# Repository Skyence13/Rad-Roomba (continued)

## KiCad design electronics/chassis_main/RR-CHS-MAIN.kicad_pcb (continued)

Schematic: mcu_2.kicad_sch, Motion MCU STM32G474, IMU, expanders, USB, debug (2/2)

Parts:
C152, C153, C154, C155, C156: 100n; C_0603_1608Metric; MPN CC0603KRX7R9BB104
D38: TPD4E05U06; USON-10_2.5x1.0mm_P0.5mm; MPN TPD4E05U06DQAR
F_AUX: 0.35A; Fuse_1206_3216Metric; MPN 1206L035YR
JP2: SJ open; SolderJumper-2_P1.3mm_Open_RoundedPad1.0x1.5mm; MPN SOLDER-JUMPER
J_AUX: JST GH 3p top; JST_GH_BM03B-GHS-TBT_1x03-1MP_P1.25mm_Vertical; MPN BM03B-GHS-TBT(LF)(SN)
J_NTC: JST GH 4p top; JST_GH_BM04B-GHS-TBT_1x04-1MP_P1.25mm_Vertical; MPN BM04B-GHS-TBT(LF)(SN)
R206, R207, R208, R209: 100k; R_0603_1608Metric; MPN RC0603FR-07100KL
R210: 10k; R_0603_1608Metric; MPN RC0603FR-0710KL
R211, R212, R213, R214: 2.2k; R_0603_1608Metric; MPN RC0603FR-072K2L
R215, R217, R219: 10k; R_0603_1608Metric; MPN RT0603BRD0710KL
R216, R218, R220: 1k; R_0603_1608Metric; MPN RC0603FR-071KL
RT1: 10k NTC; R_0603_1608Metric; MPN NCP18XH103F03RB
U44: TCA9535; TSSOP-24_4.4x7.8mm_P0.65mm; MPN TCA9535PWR
U45, U47: TCA9534; TSSOP-16_4.4x5mm_P0.65mm; MPN TCA9534PWR

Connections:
3V3: C152.1, C153.1, R210.1, R211.1, R212.1, R213.1, R214.1, U44.24 (VCC), U45.1 (A0), U45.16 (VDD), U47.2 (A1), U47.16 (VDD); also elsewhere on the board
BUS_CLAMP_ACTIVE: U47.7 (P3); also elsewhere on the board
CHAIN_END_RB: U44.20 (P17); also elsewhere on the board
CHG_NSMBALERT: U45.10 (P5); also elsewhere on the board
CHN6A_RB: U47.11 (P6); also elsewhere on the board
CHS_HTR_NFLT: U45.6 (P2); also elsewhere on the board
DBG_RX_C: D38.5 (D2-); also elsewhere on the board
DBG_TX_C: D38.4 (D2+); also elsewhere on the board
GND: C152.2, C153.2, C154.2, C155.2, C156.2, D38.3 (GND), D38.8 (GND), J_AUX.2, J_AUX.MP (MountPin), J_NTC.2, J_NTC.4, J_NTC.MP (MountPin), R206.2, R207.2, R208.2, R209.2, RT1.2, U44.2 (A1), U44.3 (A2), U44.12 (GND), U44.21 (A0), U45.2 (A1), U45.3 (A2), U45.8 (GND), U47.1 (A0), U47.3 (A2), U47.8 (GND); also elsewhere on the board
HEAD_HTR_NFLT: U45.5 (P1); also elsewhere on the board
HEAD_LOOP2_OK_RB: U47.6 (P2); also elsewhere on the board
HEAD_PWR_EN: U44.13 (P10); also elsewhere on the board
HEAD_PWR_NFLT: U45.4 (P0); also elsewhere on the board
I2C_SYS_SCL: R212.2, U44.22 (SCL), U45.14 (SCL), U47.14 (SCL); also elsewhere on the board
I2C_SYS_SDA: R211.2, U44.23 (SDA), U45.15 (SDA), U47.15 (SDA); also elsewhere on the board
I2C_TOF_SCL: R214.2; also elsewhere on the board
I2C_TOF_SDA: R213.2; also elsewhere on the board
LAMP_PAUSE: U44.10 (P06); also elsewhere on the board
LAMP_REARM: U44.9 (P05); also elsewhere on the board
LATCH_NC_RB: U47.4 (P0); also elsewhere on the board
LATCH_RUN_RB: U47.5 (P1); also elsewhere on the board
LED_CHARGE: U44.8 (P04); also elsewhere on the board
LED_FAULT: U44.7 (P03); also elsewhere on the board
LED_HOLD: U44.6 (P02); also elsewhere on the board
LED_MOVING: U44.5 (P01); also elsewhere on the board
LED_READY: U44.4 (P00); also elsewhere on the board
LED_STAT2: U44.11 (P07); also elsewhere on the board
LOOP_TEST_A: U47.9 (P4); also elsewhere on the board
LOOP_TEST_B: U47.12 (P7); also elsewhere on the board
NTC_BAY: D38.1 (D1+), J_NTC.1, R215.2, R216.1
NTC_BAY_ADC: C154.1, R216.2; also elsewhere on the board
NTC_BOARD_ADC: C156.1, R219.2, RT1.1; also elsewhere on the board
NTC_PACK: D38.2 (D1-), J_NTC.3, R217.2, R218.1
NTC_PACK_ADC: C155.1, R218.2; also elsewhere on the board
PMON_NALERT: R210.2, U45.11 (P6); also elsewhere on the board
SET_READY_RB: U47.10 (P5); also elsewhere on the board
SPARE_IO: J_AUX.3, R220.2
SPARE_IO_R: JP2.2 (B), R220.1
SWO_SPARE: JP2.1 (A); also elsewhere on the board
TOF_MUX_NRST: R209.1, U44.19 (P16); also elsewhere on the board
TOF_XSHUT_CLIFF: R206.1, U44.16 (P13); also elsewhere on the board
TOF_XSHUT_LOOK: R207.1, U44.17 (P14); also elsewhere on the board
TOF_XSHUT_REAR: R208.1, U44.18 (P15); also elsewhere on the board
V5_CM5_NFLT: U45.9 (P4); also elsewhere on the board
V5_CM5_OFF_REQ: U44.15 (P12); also elsewhere on the board
V5_PGOOD: U45.12 (P7); also elsewhere on the board
V12_AUX: F_AUX.2, J_AUX.1; also elsewhere on the board
V12_LIDAR_EN: U44.14 (P11); also elsewhere on the board
V12_LIDAR_NFLT: U45.7 (P3); also elsewhere on the board
VBAT_SW: F_AUX.1; also elsewhere on the board
VREF_3V0: R215.1, R217.1, R219.1; also elsewhere on the board

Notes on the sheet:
Motion MCU STM32G474, IMU, expanders, USB, debug (2/2)

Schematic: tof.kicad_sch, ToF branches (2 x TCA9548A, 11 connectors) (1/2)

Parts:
C157, C158, C159, C160, C161, C162, C163, C164: 100n; C_0603_1608Metric; MPN CC0603KRX7R9BB104
D39, D40, D41, D42, D43: TPD4E05U06; USON-10_2.5x1.0mm_P0.5mm; MPN TPD4E05U06DQAR
FB5, FB6, FB7, FB8, FB9, FB10: 600R; L_0603_1608Metric; MPN BLM18KG601SN1D
J_TOF0, J_TOF1, J_TOF2, J_TOF3, J_TOF4, J_TOF5: JST GH 6p top; JST_GH_BM06B-GHS-TBT_1x06-1MP_P1.25mm_Vertical; MPN BM06B-GHS-TBT(LF)(SN)
R221, R222, R226, R227, R231, R232, R236, R237, R241, R242, R246: 100; R_0603_1608Metric; MPN RC0603FR-07100RL
R223, R224, R228, R229, R233, R234, R238, R239, R243, R244: 2.2k; R_0603_1608Metric; MPN RC0603FR-072K2L
R225, R230, R235, R240, R245: 1k; R_0603_1608Metric; MPN RC0603FR-071KL
TP12: TOF0_GPIO1; TestPoint_Keystone_5019_Miniature; MPN 5019
TP13: TOF1_GPIO1; TestPoint_Keystone_5019_Miniature; MPN 5019
TP14: TOF2_GPIO1; TestPoint_Keystone_5019_Miniature; MPN 5019
TP15: TOF3_GPIO1; TestPoint_Keystone_5019_Miniature; MPN 5019
TP16: TOF4_GPIO1; TestPoint_Keystone_5019_Miniature; MPN 5019
U50, U51: TCA9548A; TSSOP-24_4.4x7.8mm_P0.65mm; MPN TCA9548APWR

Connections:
3V3: C157.1, C158.1, FB5.1, FB6.1, FB7.1, FB8.1, FB9.1, FB10.1, R223.1, R224.1, R228.1, R229.1, R233.1, R234.1, R238.1, R239.1, R243.1, R244.1, U50.24 (VCC), U51.1 (A0), U51.24 (VCC); also elsewhere on the board
GND: C157.2, C158.2, C159.2, C160.2, C161.2, C162.2, C163.2, C164.2, D39.3 (GND), D39.8 (GND), D40.3 (GND), D40.8 (GND), D41.3 (GND), D41.8 (GND), D42.3 (GND), D42.8 (GND), D43.3 (GND), D43.8 (GND), J_TOF0.2, J_TOF0.MP (MountPin), J_TOF1.2, J_TOF1.MP (MountPin), J_TOF2.2, J_TOF2.MP (MountPin), J_TOF3.2, J_TOF3.MP (MountPin), J_TOF4.2, J_TOF4.MP (MountPin), J_TOF5.2, J_TOF5.MP (MountPin), U50.1 (A0), U50.2 (A1), U50.12 (GND), U50.21 (A2), U51.2 (A1), U51.12 (GND), U51.21 (A2); also elsewhere on the board
I2C_TOF_SCL: U50.22 (SCL), U51.22 (SCL); also elsewhere on the board
I2C_TOF_SDA: U50.23 (SDA), U51.23 (SDA); also elsewhere on the board
TOF0_3V3: C159.1, FB5.2, J_TOF0.1
TOF0_GPIO1: D39.5 (D2-), J_TOF0.6, TP12.1
TOF00_SCL: R222.1, R224.2, U50.5 (SC0)
TOF0_SCL_C: D39.2 (D1-), J_TOF0.4, R222.2
TOF00_SDA: R221.1, R223.2, U50.4 (SD0)
TOF0_SDA_C: D39.1 (D1+), J_TOF0.3, R221.2
TOF0_XSHUT_C: D39.4 (D2+), J_TOF0.5, R225.2
TOF1_3V3: C160.1, FB6.2, J_TOF1.1
TOF1_GPIO1: D40.5 (D2-), J_TOF1.6, TP13.1
TOF01_SCL: R232.1, R234.2, U50.7 (SC1)
TOF1_SCL_C: D40.2 (D1-), J_TOF1.4, R227.2
TOF01_SDA: R231.1, R233.2, U50.6 (SD1)
TOF1_SDA_C: D40.1 (D1+), J_TOF1.3, R226.2
TOF1_XSHUT_C: D40.4 (D2+), J_TOF1.5, R230.2
TOF2_3V3: C161.1, FB7.2, J_TOF2.1
TOF2_GPIO1: D41.5 (D2-), J_TOF2.6, TP14.1
TOF02_SCL: R242.1, R244.2, U50.9 (SC2)
TOF2_SCL_C: D41.2 (D1-), J_TOF2.4, R232.2
TOF02_SDA: R241.1, R243.2, U50.8 (SD2)
TOF2_SDA_C: D41.1 (D1+), J_TOF2.3, R231.2
TOF2_XSHUT_C: D41.4 (D2+), J_TOF2.5, R235.2
TOF3_3V3: C162.1, FB8.2, J_TOF3.1
TOF3_GPIO1: D42.5 (D2-), J_TOF3.6, TP15.1
TOF03_SCL: U50.11 (SC3); also elsewhere on the board
TOF3_SCL_C: D42.2 (D1-), J_TOF3.4, R237.2
TOF03_SDA: U50.10 (SD3); also elsewhere on the board
TOF3_SDA_C: D42.1 (D1+), J_TOF3.3, R236.2
TOF3_XSHUT_C: D42.4 (D2+), J_TOF3.5, R240.2
TOF4_3V3: C163.1, FB9.2, J_TOF4.1
TOF4_GPIO1: D43.5 (D2-), J_TOF4.6, TP16.1
TOF04_SCL: U50.14 (SC4); also elsewhere on the board
TOF4_SCL_C: D43.2 (D1-), J_TOF4.4, R242.2
TOF04_SDA: U50.13 (SD4); also elsewhere on the board
TOF4_SDA_C: D43.1 (D1+), J_TOF4.3, R241.2
TOF4_XSHUT_C: D43.4 (D2+), J_TOF4.5, R245.2
TOF5_3V3: C164.1, FB10.2, J_TOF5.1
TOF5_GPIO1: J_TOF5.6; also elsewhere on the board
TOF05_SCL: U50.16 (SC5); also elsewhere on the board
TOF5_SCL_C: J_TOF5.4; also elsewhere on the board
TOF05_SDA: U50.15 (SD5); also elsewhere on the board
TOF5_SDA_C: J_TOF5.3, R246.2; also elsewhere on the board
TOF5_XSHUT_C: J_TOF5.5; also elsewhere on the board
TOF10_SCL: R227.1, R229.2, U51.5 (SC0)
TOF10_SDA: R226.1, R228.2, U51.4 (SD0)
TOF11_SCL: R237.1, R239.2, U51.7 (SC1)
TOF11_SDA: R236.1, R238.2, U51.6 (SD1)
TOF12_SCL: U51.9 (SC2); also elsewhere on the board
TOF12_SDA: R246.1, U51.8 (SD2); also elsewhere on the board
TOF13_SCL: U51.11 (SC3); also elsewhere on the board
TOF13_SDA: U51.10 (SD3); also elsewhere on the board
TOF14_SCL: U51.14 (SC4); also elsewhere on the board
TOF14_SDA: U51.13 (SD4); also elsewhere on the board
TOF_MUX_NRST: U50.3 (~RESET), U51.3 (~RESET); also elsewhere on the board
TOF_XSHUT_CLIFF: R225.1, R230.1, R235.1, R240.1; also elsewhere on the board
TOF_XSHUT_LOOK: R245.1; also elsewhere on the board

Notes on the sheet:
ToF branches (2 x TCA9548A, 11 connectors) (1/2)

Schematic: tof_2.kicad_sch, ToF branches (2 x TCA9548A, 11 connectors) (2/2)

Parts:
C165, C166, C167, C168, C169: 100n; C_0603_1608Metric; MPN CC0603KRX7R9BB104
D44, D45, D46, D47, D48, D49: TPD4E05U06; USON-10_2.5x1.0mm_P0.5mm; MPN TPD4E05U06DQAR
FB11, FB12, FB13, FB14, FB15: 600R; L_0603_1608Metric; MPN BLM18KG601SN1D
J_TOF6, J_TOF7, J_TOF8, J_TOF9, J_TOF10: JST GH 6p top; JST_GH_BM06B-GHS-TBT_1x06-1MP_P1.25mm_Vertical; MPN BM06B-GHS-TBT(LF)(SN)
R247, R251, R252, R256, R257, R261, R262, R266, R267, R271, R272: 100; R_0603_1608Metric; MPN RC0603FR-07100RL
R248, R249, R253, R254, R258, R259, R263, R264, R268, R269, R273, R274: 2.2k; R_0603_1608Metric; MPN RC0603FR-072K2L
R250, R255, R260, R265, R270, R275: 1k; R_0603_1608Metric; MPN RC0603FR-071KL
TP17: TOF5_GPIO1; TestPoint_Keystone_5019_Miniature; MPN 5019
TP18: TOF6_GPIO1; TestPoint_Keystone_5019_Miniature; MPN 5019
TP19: TOF7_GPIO1; TestPoint_Keystone_5019_Miniature; MPN 5019
TP20: TOF8_GPIO1; TestPoint_Keystone_5019_Miniature; MPN 5019
TP21: TOF9_GPIO1; TestPoint_Keystone_5019_Miniature; MPN 5019
TP22: TOF10_GPIO1; TestPoint_Keystone_5019_Miniature; MPN 5019

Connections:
3V3: FB11.1, FB12.1, FB13.1, FB14.1, FB15.1, R248.1, R249.1, R253.1, R254.1, R258.1, R259.1, R263.1, R264.1, R268.1, R269.1, R273.1, R274.1; also elsewhere on the board
GND: C165.2, C166.2, C167.2, C168.2, C169.2, D44.3 (GND), D44.8 (GND), D45.3 (GND), D45.8 (GND), D46.3 (GND), D46.8 (GND), D47.3 (GND), D47.8 (GND), D48.3 (GND), D48.8 (GND), D49.3 (GND), D49.8 (GND), J_TOF6.2, J_TOF6.MP (MountPin), J_TOF7.2, J_TOF7.MP (MountPin), J_TOF8.2, J_TOF8.MP (MountPin), J_TOF9.2, J_TOF9.MP (MountPin), J_TOF10.2, J_TOF10.MP (MountPin); also elsewhere on the board
TOF03_SCL: R252.1, R254.2; also elsewhere on the board
TOF03_SDA: R251.1, R253.2; also elsewhere on the board
TOF04_SCL: R262.1, R264.2; also elsewhere on the board
TOF04_SDA: R261.1, R263.2; also elsewhere on the board
TOF5_GPIO1: D44.5 (D2-), TP17.1; also elsewhere on the board
TOF05_SCL: R272.1, R274.2; also elsewhere on the board
TOF5_SCL_C: D44.2 (D1-), R247.2; also elsewhere on the board
TOF05_SDA: R271.1, R273.2; also elsewhere on the board
TOF5_SDA_C: D44.1 (D1+); also elsewhere on the board
TOF5_XSHUT_C: D44.4 (D2+), R250.2; also elsewhere on the board
TOF6_3V3: C165.1, FB11.2, J_TOF6.1
TOF6_GPIO1: D45.5 (D2-), J_TOF6.6, TP18.1
TOF6_SCL_C: D45.2 (D1-), J_TOF6.4, R252.2
TOF6_SDA_C: D45.1 (D1+), J_TOF6.3, R251.2
TOF6_XSHUT_C: D45.4 (D2+), J_TOF6.5, R255.2
TOF7_3V3: C166.1, FB12.2, J_TOF7.1
TOF7_GPIO1: D46.5 (D2-), J_TOF7.6, TP19.1
TOF7_SCL_C: D46.2 (D1-), J_TOF7.4, R257.2
TOF7_SDA_C: D46.1 (D1+), J_TOF7.3, R256.2
TOF7_XSHUT_C: D46.4 (D2+), J_TOF7.5, R260.2
TOF8_3V3: C167.1, FB13.2, J_TOF8.1
TOF8_GPIO1: D47.5 (D2-), J_TOF8.6, TP20.1
TOF8_SCL_C: D47.2 (D1-), J_TOF8.4, R262.2
TOF8_SDA_C: D47.1 (D1+), J_TOF8.3, R261.2
TOF8_XSHUT_C: D47.4 (D2+), J_TOF8.5, R265.2
TOF9_3V3: C168.1, FB14.2, J_TOF9.1
TOF9_GPIO1: D48.5 (D2-), J_TOF9.6, TP21.1
TOF9_SCL_C: D48.2 (D1-), J_TOF9.4, R267.2
TOF9_SDA_C: D48.1 (D1+), J_TOF9.3, R266.2
TOF9_XSHUT_C: D48.4 (D2+), J_TOF9.5, R270.2
TOF10_3V3: C169.1, FB15.2, J_TOF10.1
TOF10_GPIO1: D49.5 (D2-), J_TOF10.6, TP22.1
TOF10_SCL_C: D49.2 (D1-), J_TOF10.4, R272.2
TOF10_SDA_C: D49.1 (D1+), J_TOF10.3, R271.2
TOF10_XSHUT_C: D49.4 (D2+), J_TOF10.5, R275.2
TOF12_SCL: R247.1, R249.2; also elsewhere on the board
TOF12_SDA: R248.2; also elsewhere on the board
TOF13_SCL: R257.1, R259.2; also elsewhere on the board
TOF13_SDA: R256.1, R258.2; also elsewhere on the board
TOF14_SCL: R267.1, R269.2; also elsewhere on the board
TOF14_SDA: R266.1, R268.2; also elsewhere on the board
TOF_XSHUT_LOOK: R250.1, R255.1, R260.1; also elsewhere on the board
TOF_XSHUT_REAR: R265.1, R270.1, R275.1; also elsewhere on the board

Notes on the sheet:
ToF branches (2 x TCA9548A, 11 connectors) (2/2)

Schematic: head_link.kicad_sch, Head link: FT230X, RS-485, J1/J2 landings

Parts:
C170, C171: 47p; C_0603_1608Metric; MPN CC0603JRNPO9BN470
C172: 4.7u; C_0805_2012Metric; MPN GRM21BR71C475KA73L
C173, C174, C175: 100n; C_0603_1608Metric; MPN CC0603KRX7R9BB104
D50: BAT54; D_SOD-123; MPN BAT54W-7-F
D60: SM712; SOT-23; MPN SM712.TCT
FB_U: 600R; L_0603_1608Metric; MPN BLM18KG601SN1D
J_HEAD1: Mini-Fit Jr 2x5 RA; Molex_Mini-Fit_Jr_5569-10A2_2x05_P4.20mm_Horizontal; MPN 39-30-1100
J_HEAD2: JST GH 8p side; JST_GH_SM08B-GHS-TB_1x08-1MP_P1.25mm_Horizontal; MPN SM08B-GHS-TB(LF)(SN)
J_USB_HEAD: JST GH 5p top; JST_GH_BM05B-GHS-TBT_1x05-1MP_P1.25mm_Vertical; MPN BM05B-GHS-TBT(LF)(SN)
L60: CMC 90R; L_CommonModeChoke_Coilank_ACM2012; MPN ACM2012-900-2P-T002
LED2: green; LED_0603_1608Metric; MPN 150060GS75000
NT1: net tie; NetTie-2_SMD_Pad2.0mm; MPN NET-TIE
R276, R277: 27; R_0603_1608Metric; MPN RC0603FR-0727RL
R278, R279, R280: 1k; R_0603_1608Metric; MPN RC0603FR-071KL
R281, R282: 10k; R_0603_1608Metric; MPN RC0603FR-0710KL
R283: 4.7k; R_0603_1608Metric; MPN RC0603FR-074K7L
R284: 120; R_0805_2012Metric; MPN RC0805FR-07120RL
R285, R286: 560; R_0805_2012Metric; MPN RC0805FR-07560RL
R287, R288: 10; R_0805_2012Metric; MPN RC0805FR-0710RL
R289: 120; R_0805_2012Metric; MPN RC0805FR-07120RL; not fitted
R290: 10k; R_0603_1608Metric; MPN RC0603FR-0710KL; not fitted
TP23: SYNC_TTL; TestPoint_Keystone_5019_Miniature; MPN 5019
U60: USBLC6-2SC6; SOT-23-6; MPN USBLC6-2SC6
U61: FT230XS; SSOP-16_3.9x4.9mm_P0.635mm; MPN FT230XS-R
U62: THVD1450; SOIC-8_3.9x4.9mm_P1.27mm; MPN THVD1450DR
U63: THVD1450; SOIC-8_3.9x4.9mm_P1.27mm; MPN THVD1450DR; not fitted

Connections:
BUS_5V: J_HEAD2.3; also elsewhere on the board
FT_3V3: C174.1, R278.1, R283.1, U61.3 (VCCIO), U61.10 (3V3OUT)
FT_DM: C171.1, R277.2, U61.9 (USBDM)
FT_DP: C170.1, R276.2, U61.8 (USBDP)
FT_LED_A: LED2.2 (A), R278.2
FT_LED_N: LED2.1 (K), U61.7 (CBUS2)
FT_RXD: D50.2 (A), R283.2, U61.4 (RXD)
FT_TXD: R279.1, U61.1 (TXD)
FT_TXDEN: R280.1, U61.15 (CBUS0); also elsewhere on the board
FT_TXDEN_R: R280.2, R281.1, U62.2 (~RE), U62.3 (DE)
FT_TXD_R: R279.2, R282.2, U62.4 (DI)
FT_VCC: C172.1, C173.1, FB_U.2, U61.11 (~RESET), U61.12 (VCC)
GND: C170.2, C171.2, C172.2, C173.2, C174.2, C175.2, D60.3 (GND), J_HEAD1.2, J_HEAD2.4, J_HEAD2.MP (MountPin), J_USB_HEAD.4, J_USB_HEAD.MP (MountPin), NT1.2, R281.2, R286.2, R290.2, U60.2 (GND), U61.5 (GND), U61.6 (~CTS), U61.13 (GND), U62.5 (GND), U63.5 (GND); also elsewhere on the board
HEAD_HTR_N: J_HEAD1.4, NT1.1
HEAD_HTR_P: J_HEAD1.3; also elsewhere on the board
HEAD_LOOP_OUT: J_HEAD1.5; also elsewhere on the board
HEAD_LOOP_RET: J_HEAD1.6; also elsewhere on the board
HEAD_PRES_ID: J_HEAD1.7; also elsewhere on the board
HEAD_PWR_P: J_HEAD1.1; also elsewhere on the board
HUSBC_DM: J_USB_HEAD.2, U60.1 (I/O1)
HUSBC_DP: J_USB_HEAD.3, U60.3 (I/O2)
HUSB_DM_R: R277.1, U60.6 (I/O1)
HUSB_DP_R: R276.1, U60.4 (I/O2)
HUSB_VBUS: FB_U.1, J_USB_HEAD.1, U60.5 (VBUS)
J2_PRES: J_HEAD2.7; also elsewhere on the board
RS485_DN: D60.2 (IO2), J_HEAD2.2, L60.3
RS485_DP: D60.1 (IO1), J_HEAD2.1, L60.2
RS_A: R284.1, R285.2, R287.1, U62.6 (A)
RS_A_L: L60.1, R287.2
RS_B: R284.2, R286.1, R288.1, U62.7 (B)
RS_B_L: L60.4, R288.2
RS_RO: D50.1 (K), U62.1 (RO); also elsewhere on the board
SYNC_N: J_HEAD2.6, R289.2, U63.7 (B)
SYNC_P: J_HEAD2.5, R289.1, U63.6 (A)
SYNC_TTL: R290.1, TP23.1, U63.4 (DI)
USB_SHLD: J_USB_HEAD.5; also elsewhere on the board
V5_AUX: C175.1, R282.1, R285.1, U62.8 (VCC), U63.2 (~RE), U63.3 (DE), U63.8 (VCC); also elsewhere on the board

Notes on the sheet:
Head link: FT230X, RS-485, J1/J2 landings
S2-02: J_HEAD1 is a Mini-Fit Jr 2x5 (AWG 18 contacts for the heater pair); pins 1-8 = J1 pins 1-8, pins 9/10 NC.

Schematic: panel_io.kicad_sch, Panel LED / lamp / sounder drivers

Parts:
J_PANEL: JST GH 10p top; JST_GH_BM10B-GHS-TBT_1x10-1MP_P1.25mm_Vertical; MPN BM10B-GHS-TBT(LF)(SN)
LED3: red; LED_0603_1608Metric; MPN 150060RS75000
Q50, Q51, Q52, Q53, Q54, Q55, Q56, Q57, Q58: BSS138; SOT-23; MPN BSS138
R291, R292, R293, R294, R295, R296, R297: 100k; R_0603_1608Metric; MPN RC0603FR-07100KL
R298: 10k; R_0603_1608Metric; MPN RC0603FR-0710KL
R299: 1k; R_0603_1608Metric; MPN RC0603FR-071KL

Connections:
3V3: R299.1; also elsewhere on the board
BUZZER: Q58.1 (G), R298.1; also elsewhere on the board
BUZ_N: J_PANEL.9, Q58.3 (D)
GND: J_PANEL.3, J_PANEL.10, J_PANEL.MP (MountPin), Q50.2 (S), Q51.2 (S), Q52.2 (S), Q53.2 (S), Q54.2 (S), Q55.2 (S), Q56.2 (S), Q57.2 (S), Q58.2 (S), R291.2, R292.2, R293.2, R294.2, R295.2, R296.2, R297.2, R298.2; also elsewhere on the board
LAMP_PAUSE: Q56.1 (G), R297.1; also elsewhere on the board
LAMP_PAUSE_K: Q56.3 (D); also elsewhere on the board
LAMP_REARM: Q55.1 (G), R296.1; also elsewhere on the board
LAMP_REARM_K: Q55.3 (D); also elsewhere on the board
LED_CHARGE: Q54.1 (G), R295.1; also elsewhere on the board
LED_CHARGE_K: J_PANEL.8, Q54.3 (D)
LED_FAULT: Q53.1 (G), R294.1; also elsewhere on the board
LED_FAULT_K: J_PANEL.7, Q53.3 (D), Q57.3 (D)
LED_HOLD: Q52.1 (G), R293.1; also elsewhere on the board
LED_HOLD_K: J_PANEL.6, Q52.3 (D)
LED_MOVING: Q51.1 (G), R292.1; also elsewhere on the board
LED_MOVING_K: J_PANEL.5, Q51.3 (D)
LED_READY: Q50.1 (G), R291.1; also elsewhere on the board
LED_READY_K: J_PANEL.4, Q50.3 (D)
LED_STAT2: LED3.1 (K); also elsewhere on the board
LED_STAT2_A: LED3.2 (A), R299.2
V5_AUX: J_PANEL.1; also elsewhere on the board
V12_AUX: J_PANEL.2; also elsewhere on the board
WDG_FAULT: Q57.1 (G); also elsewhere on the board

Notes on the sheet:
Panel LED / lamp / sounder drivers

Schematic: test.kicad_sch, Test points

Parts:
TP24: WDG_STROBE; TestPoint_Keystone_5019_Miniature; MPN 5019
TP25: WDG_OK; TestPoint_Keystone_5019_Miniature; MPN 5019
TP26: ARM_PERMIT; TestPoint_Keystone_5019_Miniature; MPN 5019
TP27: HW_LATCH_RB; TestPoint_Keystone_5019_Miniature; MPN 5019
TP28: VMOT_SENSE; TestPoint_Keystone_5019_Miniature; MPN 5019
TP29: IPROPI_L; TestPoint_Keystone_5019_Miniature; MPN 5019
TP30: IPROPI_R; TestPoint_Keystone_5019_Miniature; MPN 5019
TP31: SPI1_SCK; TestPoint_Keystone_5019_Miniature; MPN 5019
TP32: SPI1_MISO; TestPoint_Keystone_5019_Miniature; MPN 5019
TP33: SPI1_MOSI; TestPoint_Keystone_5019_Miniature; MPN 5019
TP34: I2C_SYS_SDA; TestPoint_Keystone_5019_Miniature; MPN 5019
TP35: I2C_SYS_SCL; TestPoint_Keystone_5019_Miniature; MPN 5019
TP36: I2C_TOF_SDA; TestPoint_Keystone_5019_Miniature; MPN 5019
TP37: I2C_TOF_SCL; TestPoint_Keystone_5019_Miniature; MPN 5019
TP38: CHAIN_END; TestPoint_Keystone_5019_Miniature; MPN 5019
TP39: RUN_12V; TestPoint_Keystone_5019_Miniature; MPN 5019
TP40: COIL_RTN; TestPoint_Keystone_5019_Miniature; MPN 5019
TP41: VBAT_SW; TestPoint_Keystone_5019_Miniature; MPN 5019
TP42: VSYS; TestPoint_Keystone_5019_Miniature; MPN 5019
TP43: V5_CM5; TestPoint_Keystone_5019_Miniature; MPN 5019
TP44: 3V3; TestPoint_Keystone_5019_Miniature; MPN 5019
TP45: V5_AUX; TestPoint_Keystone_5019_Miniature; MPN 5019
TP46: VREF_3V0; TestPoint_Keystone_5019_Miniature; MPN 5019
TP47: VMOT; TestPoint_Keystone_5019_Miniature; MPN 5019
TP48, TP49: GND; TestPoint_Keystone_5019_Miniature; MPN 5019
TP50: CH_N0; TestPoint_Keystone_5019_Miniature; MPN 5019
TP51: EN_SYS; TestPoint_Keystone_5019_Miniature; MPN 5019
TP52: LOOP_F; TestPoint_Keystone_5019_Miniature; MPN 5019
TP53: PRES_F; TestPoint_Keystone_5019_Miniature; MPN 5019
TP54: CHG_TEMP_OK; TestPoint_Keystone_5019_Miniature; MPN 5019
TP55: CLAMP_G; TestPoint_Keystone_5019_Miniature; MPN 5019
TP56: FT_TXDEN; TestPoint_Keystone_5019_Miniature; MPN 5019
TP57: RS_RO; TestPoint_Keystone_5019_Miniature; MPN 5019
TP58: U3_NTC; TestPoint_Keystone_5019_Miniature; MPN 5019
TP59: V12_AUX; TestPoint_Keystone_5019_Miniature; MPN 5019
TP60: CH_N6A; TestPoint_Keystone_5019_Miniature; MPN 5019
TP61: K1_RUN; TestPoint_Keystone_5019_Miniature; MPN 5019
TP62: RELAY_RTN; TestPoint_Keystone_5019_Miniature; MPN 5019
TP63: SVC1 GND; TestPoint_Pad_D1.5mm; MPN TEST-PAD
TP64: SVC2 SVC_CHAIN_END; TestPoint_Pad_D1.5mm; MPN TEST-PAD
TP65: SVC3 SVC_K1_RUN; TestPoint_Pad_D1.5mm; MPN TEST-PAD
TP66: SVC4 SVC_RUN_HD; TestPoint_Pad_D1.5mm; MPN TEST-PAD
TP67: SVC5 SVC_RUN_12V; TestPoint_Pad_D1.5mm; MPN TEST-PAD
TP68: SVC6 SVC_RELAY_RTN; TestPoint_Pad_D1.5mm; MPN TEST-PAD
TP69: SVC7 SVC_HOLD_A; TestPoint_Pad_D1.5mm; MPN TEST-PAD
TP70: SVC8 SVC_LS_A; TestPoint_Pad_D1.5mm; MPN TEST-PAD
TP71: SVC9 SVC_CH_N6A; TestPoint_Pad_D1.5mm; MPN TEST-PAD
TP72: SVC10 SVC_SET_CAP; TestPoint_Pad_D1.5mm; MPN TEST-PAD

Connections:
3V3: TP44.1; also elsewhere on the board
ARM_PERMIT: TP26.1; also elsewhere on the board
CHAIN_END: TP38.1; also elsewhere on the board
CHG_TEMP_OK: TP54.1; also elsewhere on the board
CH_N0: TP50.1; also elsewhere on the board
CH_N6A: TP60.1; also elsewhere on the board
CLAMP_G: TP55.1; also elsewhere on the board
COIL_RTN: TP40.1; also elsewhere on the board
EN_SYS: TP51.1; also elsewhere on the board
FT_TXDEN: TP56.1; also elsewhere on the board
GND: TP48.1, TP49.1, TP63.1; also elsewhere on the board
HW_LATCH_RB: TP27.1; also elsewhere on the board
I2C_SYS_SCL: TP35.1; also elsewhere on the board
I2C_SYS_SDA: TP34.1; also elsewhere on the board
I2C_TOF_SCL: TP37.1; also elsewhere on the board
I2C_TOF_SDA: TP36.1; also elsewhere on the board
IPROPI_L: TP29.1; also elsewhere on the board
IPROPI_R: TP30.1; also elsewhere on the board
K1_RUN: TP61.1; also elsewhere on the board
LOOP_F: TP52.1; also elsewhere on the board
PRES_F: TP53.1; also elsewhere on the board
RELAY_RTN: TP62.1; also elsewhere on the board
RS_RO: TP57.1; also elsewhere on the board
RUN_12V: TP39.1; also elsewhere on the board
SPI1_MISO: TP32.1; also elsewhere on the board
SPI1_MOSI: TP33.1; also elsewhere on the board
SPI1_SCK: TP31.1; also elsewhere on the board
SVC_CHAIN_END: TP64.1; also elsewhere on the board
SVC_CH_N6A: TP71.1; also elsewhere on the board
SVC_HOLD_A: TP69.1; also elsewhere on the board
SVC_K1_RUN: TP65.1; also elsewhere on the board
SVC_LS_A: TP70.1; also elsewhere on the board
SVC_RELAY_RTN: TP68.1; also elsewhere on the board
SVC_RUN_12V: TP67.1; also elsewhere on the board
SVC_RUN_HD: TP66.1; also elsewhere on the board
SVC_SET_CAP: TP72.1; also elsewhere on the board
U3_NTC: TP58.1; also elsewhere on the board
V5_AUX: TP45.1; also elsewhere on the board
V5_CM5: TP43.1; also elsewhere on the board
V12_AUX: TP59.1; also elsewhere on the board
VBAT_SW: TP41.1; also elsewhere on the board
VMOT: TP47.1; also elsewhere on the board
VMOT_SENSE: TP28.1; also elsewhere on the board
VREF_3V0: TP46.1; also elsewhere on the board
VSYS: TP42.1; also elsewhere on the board
WDG_OK: TP25.1; also elsewhere on the board
WDG_STROBE: TP24.1; also elsewhere on the board

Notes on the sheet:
Test points

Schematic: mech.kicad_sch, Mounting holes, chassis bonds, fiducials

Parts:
C176, C177, C178, C179: 10n; C_0603_1608Metric; MPN CC0603KRX7R9BB103
FID1, FID2, FID3: fiducial; Fiducial_1mm_Mask2mm; MPN FIDUCIAL
H1, H2, H3, H4, H5, H6: M3; MountingHole_3.2mm_M3_Pad_Via; MPN MOUNTING-HOLE-M3
R300, R301, R302, R303: 1M; R_0603_1608Metric; MPN RC0603FR-071ML

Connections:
CHASSIS_H2: C176.1, H2.1, R300.1
CHASSIS_H4: C177.1, H4.1, R301.1
CHASSIS_H5: C178.1, H5.1, R302.1
CHASSIS_H6: C179.1, H6.1, R303.1
GND: C176.2, C177.2, C178.2, C179.2, H1.1, H3.1, R300.2, R301.2, R302.2, R303.2; also elsewhere on the board

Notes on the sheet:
Mounting holes, chassis bonds, fiducials

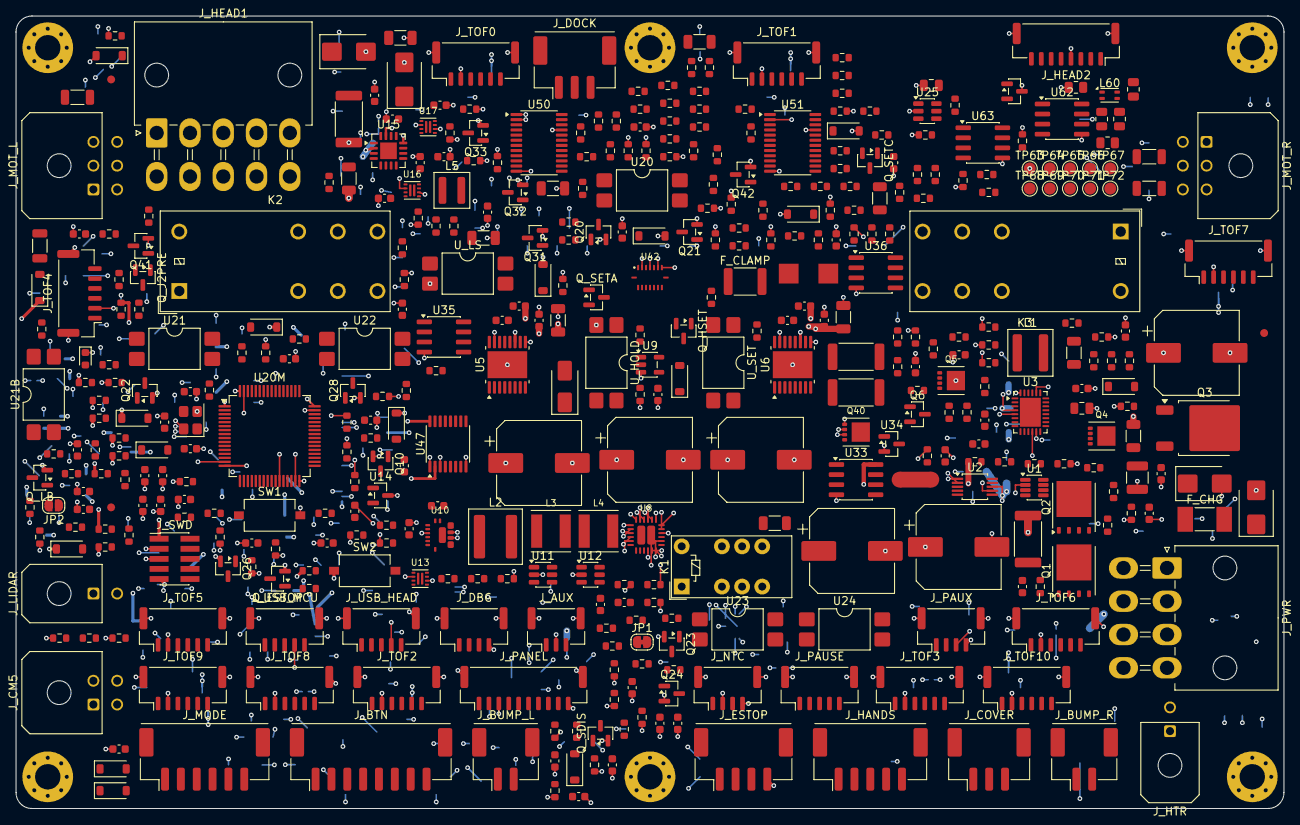
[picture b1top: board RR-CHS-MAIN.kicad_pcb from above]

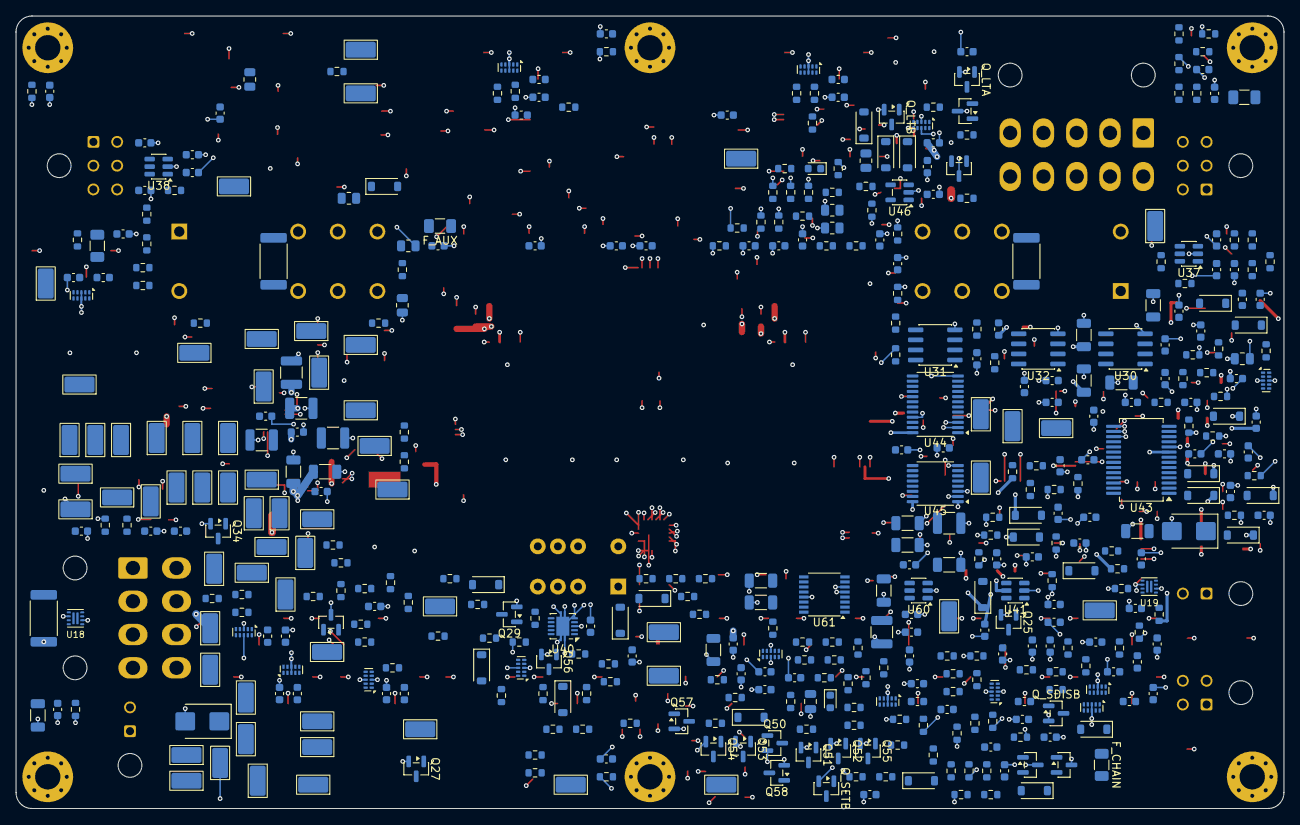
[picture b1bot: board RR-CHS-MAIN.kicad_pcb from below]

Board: 6 copper layers, 160.0 x 100.0 mm, 881 parts (455 on the bottom side), 484 nets.

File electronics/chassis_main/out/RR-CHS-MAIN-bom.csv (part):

Refs,Qty,Value,Footprint,Manufacturer,MPN,DNP,Notes
C1 C3 C4 C5 C6 C10 C12 C13 C16 C19 C24 C25 C27 C34 C35 C36 C39 C41 C45 C51 C53 C54 C57 C60 C63 C66 C75 C76 C77 C78 C81 C82 C83 C85 C86 C100 C101 C108 C109 C110 C111 C114 C116 C118 C121 C122 C126 C128 C130 C133 C134 C137 C138 C139 C140 C141 C143 C147 C149 C150 C151 C152 C153 C154 C155 C156 C157 C158 C159 C160 C161 C162 C163 C164 C165 C166 C167 C168 C169 C173 C174 C175 C_LB1 C_LB2 C_U46 C_U47,86,100n,Capacitor_SMD:C_0603_1608Metric,Yageo,CC0603KRX7R9BB104,,charge-pump capacitor: check the reference node in the datasheet (VS or SRC) [U]; inlet-voltage detect for Q21 (chain) and Q31/Q32 (head branches off while charging); CBOOT-RBOOT 0 ohm = fastest edge; raise RBOOT to slow the SW edge if EMI requires; 1 ms
C2 C58 C61 C87 C88 C89 C90 C91 C92 C93 C94 C95 C96 C97 C115 C127 C_KR C_N6A C_U9T,19,22n,Capacitor_SMD:C_0603_1608Metric,Yageo,CC0603KRX7R9BB223,,output slew control
C7 C105 C106 C107,4,270u,Capacitor_SMD:CP_Elec_10x10.5,Panasonic,EEHZA1V271P,,"VBAT_SW bulk; VMOT bulk, ripple-rated, -55 C; verify: true"
C8 C9 C67 C68 C69 C70 C71 C117 C129,9,10u,Capacitor_SMD:C_1206_3216Metric,Murata,GRM31CR71E106KA12L,,verify: true
C11 C17 C18 C32 C33,5,10u,Capacitor_SMD:C_1210_3225Metric,Murata,GRM32ER71H106KA12L,,verify: true
C14 C73 C142 C172,4,4.7u,Capacitor_SMD:C_0805_2012Metric,Murata,GRM21BR71C475KA73L,,verify: true
C15 C26 C49 C50 C52 C72 C144 C_SC C_SDB,9,1u,Capacitor_SMD:C_0603_1608Metric,Murata,GRM188R71C105KA12D,,AC coupling: one gate pulse per closing edge (tau 110 ms with R_SG + R_SSER); permit dips < 41 ms do not cost C_SET charge; verify: true
C20 C_SET,2,100u,Capacitor_SMD:CP_Elec_10x10.5,Panasonic,EEHZA1H101P,,VSYS bulk (24 V while charging); set-pulse capacitor (-55 C rated); verify: true
C21 C22,2,22u,Capacitor_SMD:C_1210_3225Metric,Murata,GRM32ER71E226KE15L,,verify: true
C23,1,10n,Capacitor_SMD:C_0603_1608Metric,Yageo,CC0603KRX7R9BB103,DNP,
C28 C145 C146,3,10p,Capacitor_SMD:C_0603_1608Metric,Yageo,CC0603JRNPO9BN100,,
C29 C30 C31 C40 C43 C44 C47 C48,8,22u,Capacitor_SMD:C_1206_3216Metric,Murata,GRM31CR71A226KE15L,,verify: true
C37,1,3.3n,Capacitor_SMD:C_0603_1608Metric,Yageo,CC0603KRX7R9BB332,,output slew control
C38 C55 C56 C59 C62 C64 C65 C74 C79 C80 C98 C99 C103 C104 C113 C125 C148 C176 C177 C178 C179 C_AG C_NC C_SD,24,10n,Capacitor_SMD:C_0603_1608Metric,Yageo,CC0603KRX7R9BB103,,over-current blanking; output slew control; soft start a few ms into 810 uF [U]
C42 C46,2,4.7u,Capacitor_SMD:C_1206_3216Metric,Murata,GRM31CR71H475KA12L,,verify: true
C84 C102 C112 C119 C120 C123 C124 C131 C132 C135 C136,11,1n,Capacitor_SMD:C_0603_1608Metric,Yageo,CC0603JRNPO9BN102,,tau 4.7 us; max edge rate 10.7 kHz
C170 C171,2,47p,Capacitor_SMD:C_0603_1608Metric,Yageo,CC0603JRNPO9BN470,,
C_SCG,1,470n,Capacitor_SMD:C_0603_1608Metric,Yageo,CC0603KRX7R7BB474,,Q_SETC stays on 37-67 ms after SET_READY falls (the dump); verify: true
C_SF,1,2.2u,Capacitor_SMD:C_0603_1608Metric,Murata,GRM188R71C225KE11D,,"S4 (N2): set qualification, the pulse cannot start before the set contact has been closed >= 3.2 ms (T13); verify: true"
D1 D4 D5 D6 D7,5,SMBJ16CA,Diode_SMD:D_SMB,Littelfuse,SMBJ16CA,,bidirectional: survives a reversed pack
D2,1,SMBJ28A,Diode_SMD:D_SMB,Littelfuse,SMBJ28A,,
D3 D30,2,Z12,Diode_SMD:D_SOD-123,Diodes Inc.,BZT52C12-7-F,,gate clamp; 10-12 V gate supply
D8,1,Z5V1,Diode_SMD:D_SOD-123,Diodes Inc.,BZT52C5V1-7-F,,clamps the gate if LINK_A is shorted to +24 V at the inlet
D9 D10 D12 D_AUX D_SET,5,PESD15VL2BT,Package_TO_SOT_SMD:SOT-23,Nexperia,"PESD15VL2BT,215",,"15 V stand-off: survives a V12_AUX short in W-018 (a 5.5 V array would not); 15 V stand-off on the REARM aux pair (replaces D29, 5.5 V): survives V12_AUX on W-018.3/.4; verify: true"
D11 D13 D16 D17 D18 D19 D20 D21 D22 D23 D24 D25 D26 D27 D28 D33 D36 D50 D_K1B D_KR D_N6A D_NC D_RB D_SCL D_SEAL D_SGN D_SRB D_U9T,28,BAT54,Diode_SMD:D_SOD-123,Diodes Inc.,BAT54W-7-F,,WDO also resets the MCU (firmware request); stops C_SET feeding the brake relays through the seal-in contact; clamps a W-018 short to V12_AUX (1.2 mA through R_SSER); negative clamp / reset on release; S5: HIGH = clamp level VDD + 0.1-0.3 V (>= 3.5 V) against VIH(max) 2.73 V; GPB2 cannot drive the aux contact node; 5 V receiver output can only pull RXD low; RXD idles at mark while the receiver is disabled during transmit
D14 D31 D34 D_HR D_LSR D_RSET,6,1N4148W,Diode_SMD:D_SOD-123,Diodes Inc.,1N4148W-7-F,,M1: C_SET charges from CHAIN_END but cannot feed it; LED reverse protection (coil kick); LED reverse protection
D15,1,Z24,Diode_SMD:D_SOD-123,Diodes Inc.,BZT52C24-7-F,,coil clamp: diode + 24 V Zener
D32 D35,2,Z20,Diode_SMD:D_SOD-123,Diodes Inc.,BZT52C20-7-F,,coil clamp: diode + 24 V Zener; verify: true
D37 D38 D39 D40 D41 D42 D43 D44 D45 D46 D47 D48 D49 D_PAUSE,14,TPD4E05U06,Package_SON:USON-10_2.5x1.0mm_P0.5mm,Texas Instruments,TPD4E05U06DQAR,,"pins 6, 7, 9, 10 flow-through NC (as D29); encoder lines (5 V); pin use as on RR-TOF-A (pins 6, 7, 9, 10 are flow-through NC)"
D60,1,SM712,Package_TO_SOT_SMD:SOT-23,Semtech,SM712.TCT,,
D_RUN,1,S1G,Diode_SMD:D_SMA,Diodes Inc.,S1G-13-F,,RUN_12V cannot back-feed RUN_HD / K1_RUN / CHAIN_END; isolates the K2/K3 kick. S4 (N5): silicon (Schottky leakage at temperature could light U_LS / U_HOLD); verify: true
F1 F2,2,0.1A,Fuse:Fuse_1206_3216Metric,Littelfuse,1206L010YR,,verify: true
FB1 FB2 FB3 FB4,4,50R 6A,Inductor_SMD:L_1206_3216Metric,Murata,BLM31SN500SN1L,,verify: true
FB5 FB6 FB7 FB8 FB9 FB10 FB11 FB12 FB13 FB14 FB15 FB_A FB_U,13,600R,Inductor_SMD:L_0603_1608Metric,Murata,BLM18KG601SN1D,,verify: true
F_AUX,1,0.35A,Fuse:Fuse_1206_3216Metric,Littelfuse,1206L035YR,,verify: true
F_CHAIN,1,0.2A,Fuse:Fuse_1206_3216Metric,Littelfuse,1206L020YR,,verify: true
F_CHG,1,5A,Fuse:Fuse_Littelfuse-NANO2-451_453,Littelfuse,0453005.MR,,
F_CLAMP,1,1.1A,Fuse:Fuse_1812_4532Metric,Littelfuse,1812L110/33GR,,verify: true
J_AUX,1,JST GH 3p top,Connector_JST:JST_GH_BM03B-GHS-TBT_1x03-1MP_P1.25mm_Vertical,JST,BM03B-GHS-TBT(LF)(SN),,JST GH is rated -25..+85 C [U]: no margin at the -25 C objective (CCR-E05)
J_BTN,1,CLIK-Mate 2.0 8p top,Connector_Molex:Molex_CLIK-Mate_502443-0870_1x08-1MP_P2.00mm_Vertical,Molex,502443-0870,,"SAFETY family. Series number recalled, not confirmed [U].; verify: true"
J_BUMP_L J_BUMP_R,2,CLIK-Mate 2.0 2p top,Connector_Molex:Molex_CLIK-Mate_502443-0270_1x02-1MP_P2.00mm_Vertical,Molex,502443-0270,,"SAFETY family. Series number recalled, not confirmed [U].; verify: true"
J_CM5,1,Micro-Fit 3.0 2x2 RA,Connector_Molex:Molex_Micro-Fit_3.0_43045-0400_2x02_P3.00mm_Horizontal,Molex,43045-0400,,POWER family. Suffix for plating/pegs to be chosen with the harness lead.; verify: true
J_COVER J_DOCK,2,CLIK-Mate 2.0 3p top,Connector_Molex:Molex_CLIK-Mate_502443-0370_1x03-1MP_P2.00mm_Vertical,Molex,502443-0370,,"SAFETY family. Series number recalled, not confirmed [U].; verify: true"
J_DBG J_NTC J_PAUX,3,JST GH 4p top,Connector_JST:JST_GH_BM04B-GHS-TBT_1x04-1MP_P1.25mm_Vertical,JST,BM04B-GHS-TBT(LF)(SN),,JST GH is rated -25..+85 C [U]: no margin at the -25 C objective (CCR-E05)
J_ESTOP,1,CLIK-Mate 2.0 4p top,Connector_Molex:Molex_CLIK-Mate_502443-0470_1x04-1MP_P2.00mm_Vertical,Molex,502443-0470,,"SAFETY family. Series number recalled, not confirmed [U].; verify: true"
J_HANDS,1,CLIK-Mate 2.0 5p top,Connector_Molex:Molex_CLIK-Mate_502443-0570_1x05-1MP_P2.00mm_Vertical,Molex,502443-0570,,"SAFETY family. Series number recalled, not confirmed [U].; verify: true"
J_HEAD1,1,Mini-Fit Jr 2x5 RA,Connector_Molex:Molex_Mini-Fit_Jr_5569-10A2_2x05_P4.20mm_Horizontal,Molex,39-30-1100,,POWER family. Suffix for plating/pegs to be chosen with the harness lead.; verify: true
J_HEAD2,1,JST GH 8p side,Connector_JST:JST_GH_SM08B-GHS-TB_1x08-1MP_P1.25mm_Horizontal,JST,SM08B-GHS-TB(LF)(SN),,JST GH is rated -25..+85 C [U]: no margin at the -25 C objective (CCR-E05)
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
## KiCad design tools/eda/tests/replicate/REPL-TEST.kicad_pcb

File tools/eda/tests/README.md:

# rrkicad generator tests (not product designs)

| dir | what | run |
|---|---|---|
| `stress/` | synthetic 4-layer 100 x 80 mm board, 150 parts, 146 auto-arranged: LQFP-64, QFN-48 0.5 mm, 20 SOT-23-5, multi-unit SOIC-8, local symbol + footprint, DNP, cut-out, keep-out, pre-route, split power plane | `python3 tools/eda/rrkicad.py build tools/eda/tests/stress/board.py` (10-20 min) |
| `stress6/` | same circuit on 6 layers, MCU decoupling on the bottom side | `... build tools/eda/tests/stress6/board.py` (1.5-3 min) |
| `replicate/` | two identical lanes via `board.replicate()` (placement + routes), `waive()` / `severity()` | `... build tools/eda/tests/replicate/board.py` (25 s; build twice to freeze the block routes) |
| `import_chassis/`, `import_panel/`, `import_head_acq/` | `rrkicad.importer.from_circuit()` on the three stage-1 `circuit.py` files, schematic + ERC only | `... sch tools/eda/tests/import_chassis/board.py` (3-17 s) |
| `scale500/` | synthetic 6-layer 160 x 100 mm, 493 parts (LQFP-100, LQFP-64, 2 QFN, 2 TSSOP, 40 SOT-23(-5), 13 edge connectors, two-sided, 0.8-1.5 mm power nets) | `... build tools/eda/tests/scale500/board.py` - generation tested only, not routed (the real boards below were the better evidence) |
| `head_escape/` | copy of the inputs of `electronics/head_acq/` (1085 parts) with escape on - routing test | `... build tools/eda/tests/head_escape/board.py --budget 2400` (about 70 min) |
| `chassis_escape/` | copy of the inputs of `electronics/chassis_main/` (771 parts) - routing test | `... build tools/eda/tests/chassis_escape/board.py --budget 2400` |

Results: `<dir>/reports/summary.json` (builds), `<dir>/route/progress.log` (one line per autorouter run), or
`reports/erc.*` + `reports/import_report.json` (imports). Measured results and their history: `tools/eda/STATUS.md`
and "Stress test and practical limits" in `tools/eda/README.md`.

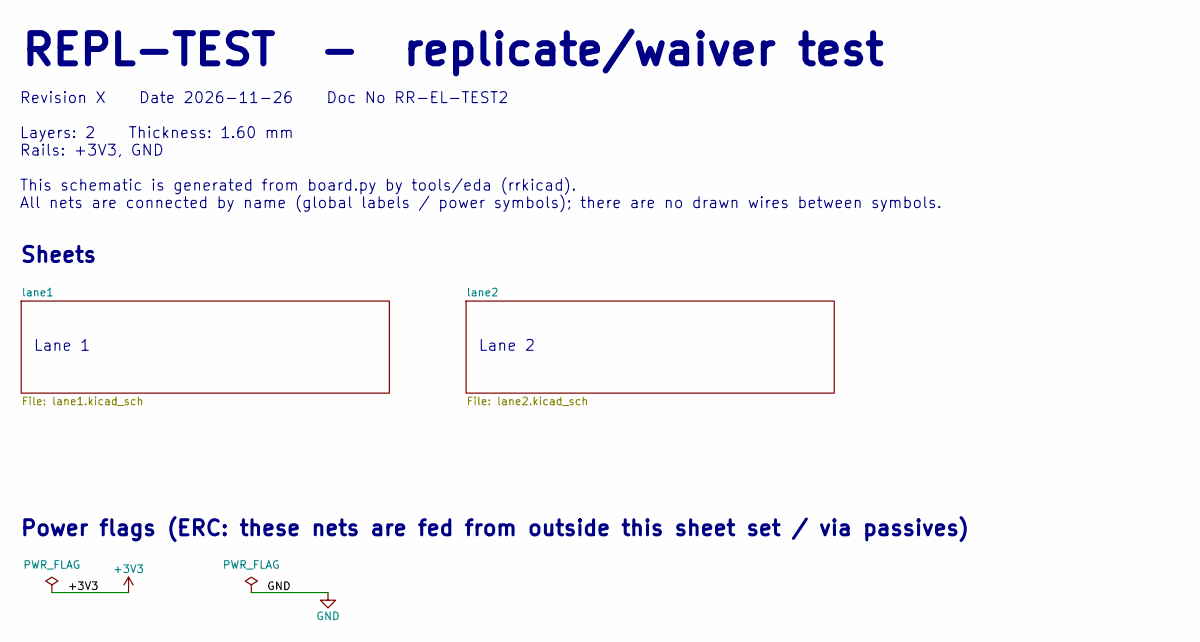
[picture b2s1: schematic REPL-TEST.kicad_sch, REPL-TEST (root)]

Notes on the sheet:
REPL-TEST - replicate/waiver test
Revision X Date 2026-11-26 Doc No RR-EL-TEST2 Layers: 2 Thickness: 1.60 mm Rails: +3V3, GND This schematic is generated from board.py by tools/eda (rrkicad). All nets are connected by name (global labels / power symbols); there are no drawn wires between symbols.
Sheets
Lane 1
Lane 2
Power flags (ERC: these nets are fed from outside this sheet set / via passives)
